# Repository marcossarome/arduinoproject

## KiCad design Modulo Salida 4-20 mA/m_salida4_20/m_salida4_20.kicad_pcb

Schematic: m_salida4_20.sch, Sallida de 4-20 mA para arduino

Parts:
C1, C2, C4: 100nF; C_Disc_D6.0mm_W2.5mm_P5.00mm
C3: 10uF; CP_Radial_D8.0mm_P5.00mm
C5: 200nF; C_Disc_D6.0mm_W2.5mm_P5.00mm
F1: 200mA; Fuseholder_Blade_ATO_Littlefuse_Pudenz_2_Pin
J1, J3: Screw_Terminal_01x02; TerminalBlock_Altech_AK300-2_P5.00mm
J2: Screw_Terminal_01x03; TerminalBlock_Altech_AK300-3_P5.00mm
Q1: 2N3904; TO-92_Inline
Q2: 2N2219; TO-39-3
R1, R3: 27k; R_Axial_DIN0204_L3.6mm_D1.6mm_P5.08mm_Horizontal
R2: 47k; R_Axial_DIN0204_L3.6mm_D1.6mm_P5.08mm_Horizontal
R4: 6.2k; R_Axial_DIN0204_L3.6mm_D1.6mm_P5.08mm_Horizontal
R5: 10k; R_Axial_DIN0204_L3.6mm_D1.6mm_P5.08mm_Horizontal
R6, R7: 100k; R_Axial_DIN0204_L3.6mm_D1.6mm_P5.08mm_Horizontal
R8: 1k; R_Axial_DIN0204_L3.6mm_D1.6mm_P5.08mm_Horizontal
R9: 270; R_Axial_DIN0204_L3.6mm_D1.6mm_P5.08mm_Horizontal
R10: 1.8k; R_Axial_DIN0204_L3.6mm_D1.6mm_P5.08mm_Horizontal
RV1: 1k; Potentiometer_Bourns_3296X_Horizontal
RV2: 10k; Potentiometer_Bourns_3296X_Horizontal
RV3: 30V; RV_Disc_D7mm_W3.6mm_P5mm
U1: LM324; DIP-14_W7.62mm_Socket_LongPads

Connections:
+5V: C1.1, J2.2, R3.1, R5.1
+24V: C2.1, C3.1, F1.2, J3.1, RV3.1, U1.4 (V+)
GND: C1.2, C2.2, C3.2, C4.2, J2.3, R2.2, R4.2, RV2.2, RV2.3, RV3.2, U1.11 (V-)
unnamed: C4.1, C5.2, R6.1, R7.2
unnamed: C5.1, U1.9 (-)
unnamed: F1.1, J2.1
unnamed: J1.2, R1.2
unnamed: J3.2, Q2.3
unnamed: Q1.1, U1.1, U1.2 (-)
unnamed: Q1.2, R1.1, R2.1
unnamed: Q1.3, R5.2, U1.5 (+)
unnamed: Q2.1, R9.1, R10.1, U1.13 (-)
unnamed: Q2.2, R8.1
unnamed: R3.2, RV1.1
unnamed: R4.1, RV1.3
unnamed: R6.2, U1.6 (-), U1.7
unnamed: R7.1, U1.10 (+)
unnamed: R8.2, U1.14
unnamed: R9.2, R10.2, RV2.1
unnamed: RV1.2, U1.3 (+)
unnamed: U1.8, U1.12 (+)

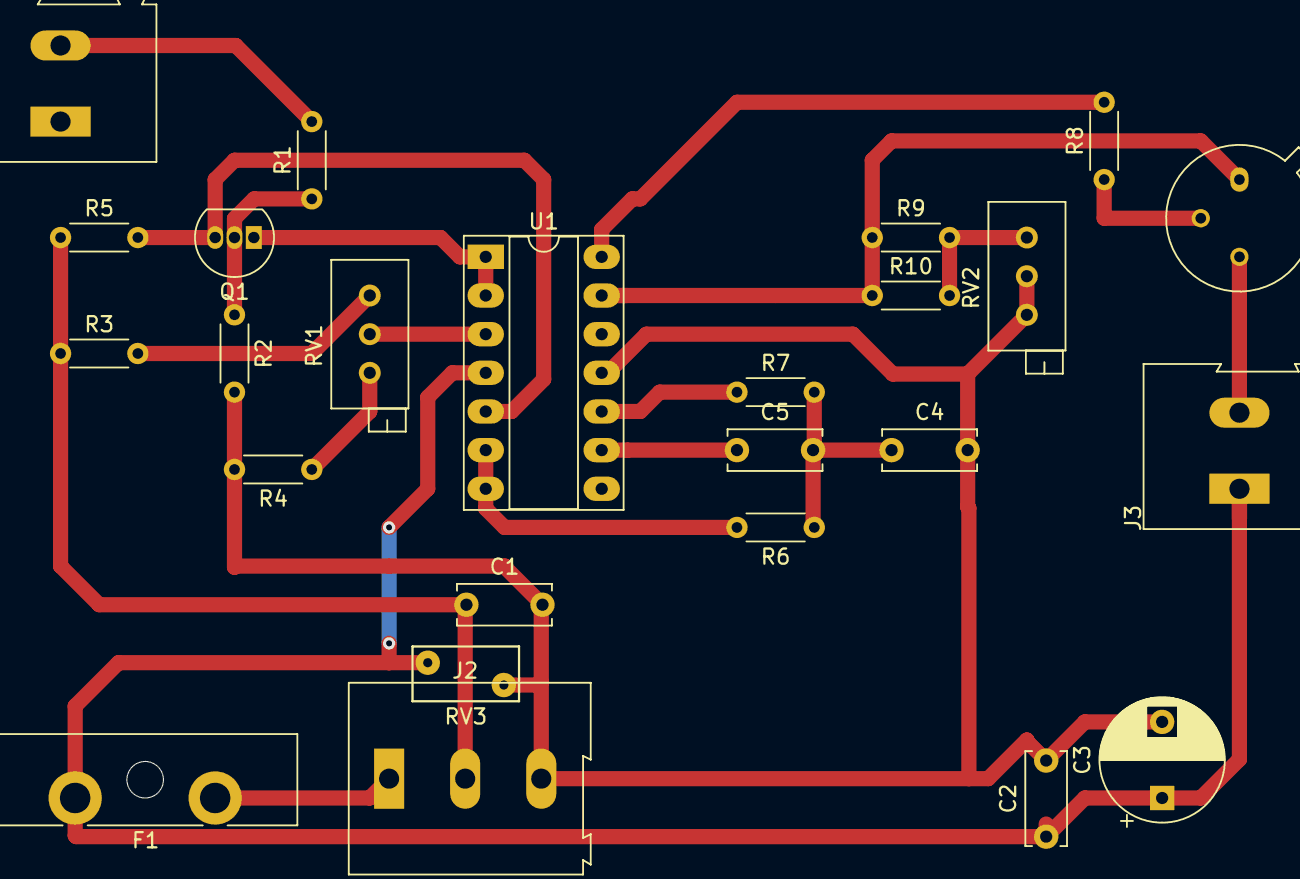
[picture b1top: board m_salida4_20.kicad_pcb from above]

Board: 2 copper layers, 25 parts (0 on the bottom side), 21 nets.

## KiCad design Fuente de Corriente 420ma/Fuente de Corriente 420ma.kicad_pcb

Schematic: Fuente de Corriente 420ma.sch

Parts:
C1: 10uF/35V; CP_Radial_D5.0mm_P2.50mm
C2: 10uF/25V; CP_Radial_D5.0mm_P2.50mm
C3: 0.1uF; C_Disc_D5.0mm_W2.5mm_P2.50mm
C4: 0,1uF; C_Disc_D5.0mm_W2.5mm_P2.50mm
C5: 100pF; C_Disc_D5.0mm_W2.5mm_P2.50mm
J1, J2: Screw_Terminal_01x02; TerminalBlock_Phoenix_MKDS-1,5-2-5.08_1x02_P5.08mm_Horizont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
Q1: 2N3906; TO-92
R1: 39k; R_Axial_DIN0207_L6.3mm_D2.5mm_P7.62mm_Horizontal
R2: 100; R_Axial_DIN0207_L6.3mm_D2.5mm_P15.24mm_Horizontal
R3: 10K; R_Axial_DIN0207_L6.3mm_D2.5mm_P15.24mm_Horizontal
RV1: 10k; Potentiometer_Bourns_3296W_Vertical
RV2: 10k; TerminalBlock_Phoenix_MKDS-1,5-3_1x03_P5.00mm_Horizontal
RV3: 1k; Potentiometer_Bourns_3266Y_Vertical
U1: LM7812_TO220; TO-220-3_Vertical
U2: LM324; DIP-14_W7.62mm_Socket

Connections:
GND: C1.2, C2.2, C3.2, C4.2, J1.2, J2.1, R1.2, U1.2 (GND), U2.11 (V-)
unnamed: C2.1, C3.1, R2.2, RV1.1, U1.3 (VO), U2.4 (V+)
unnamed: C4.1, RV2.2, U2.2 (-)
unnamed: C5.1, R3.2, U2.3 (+)
unnamed: C5.2, Q1.2, U2.1
unnamed: J1.1, Q1.1
unnamed: Q1.3, R2.1, R3.1
unnamed: R1.1, RV3.2, RV3.3
unnamed: RV1.2, RV1.3, RV2.1
unnamed: RV2.3, RV3.1
VCC: C1.1, J2.2, U1.1 (VI)

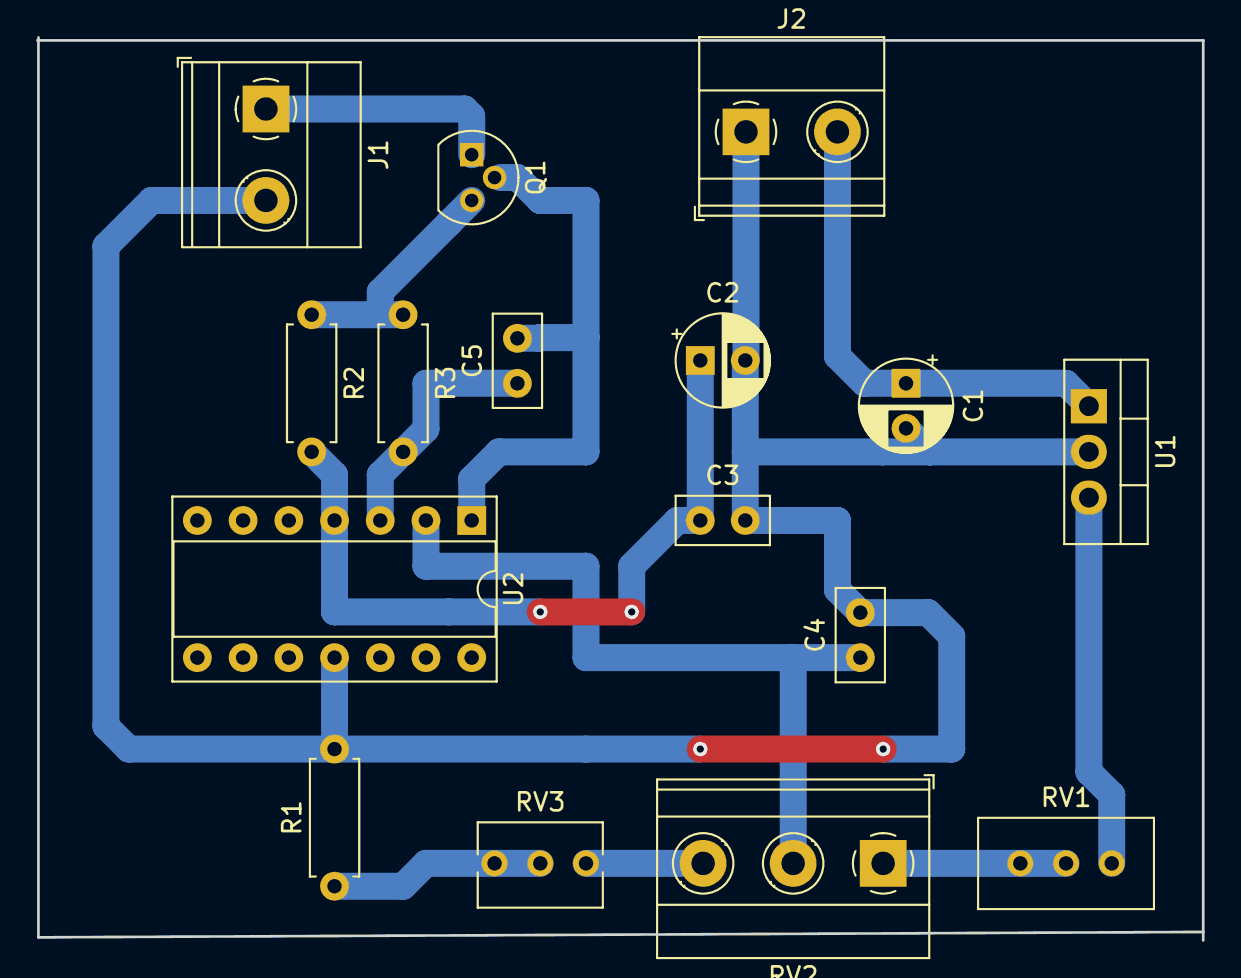
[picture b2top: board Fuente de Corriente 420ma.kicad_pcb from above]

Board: 2 copper layers, 64.8 x 50.2 mm, 16 parts (0 on the bottom side), 11 nets.
